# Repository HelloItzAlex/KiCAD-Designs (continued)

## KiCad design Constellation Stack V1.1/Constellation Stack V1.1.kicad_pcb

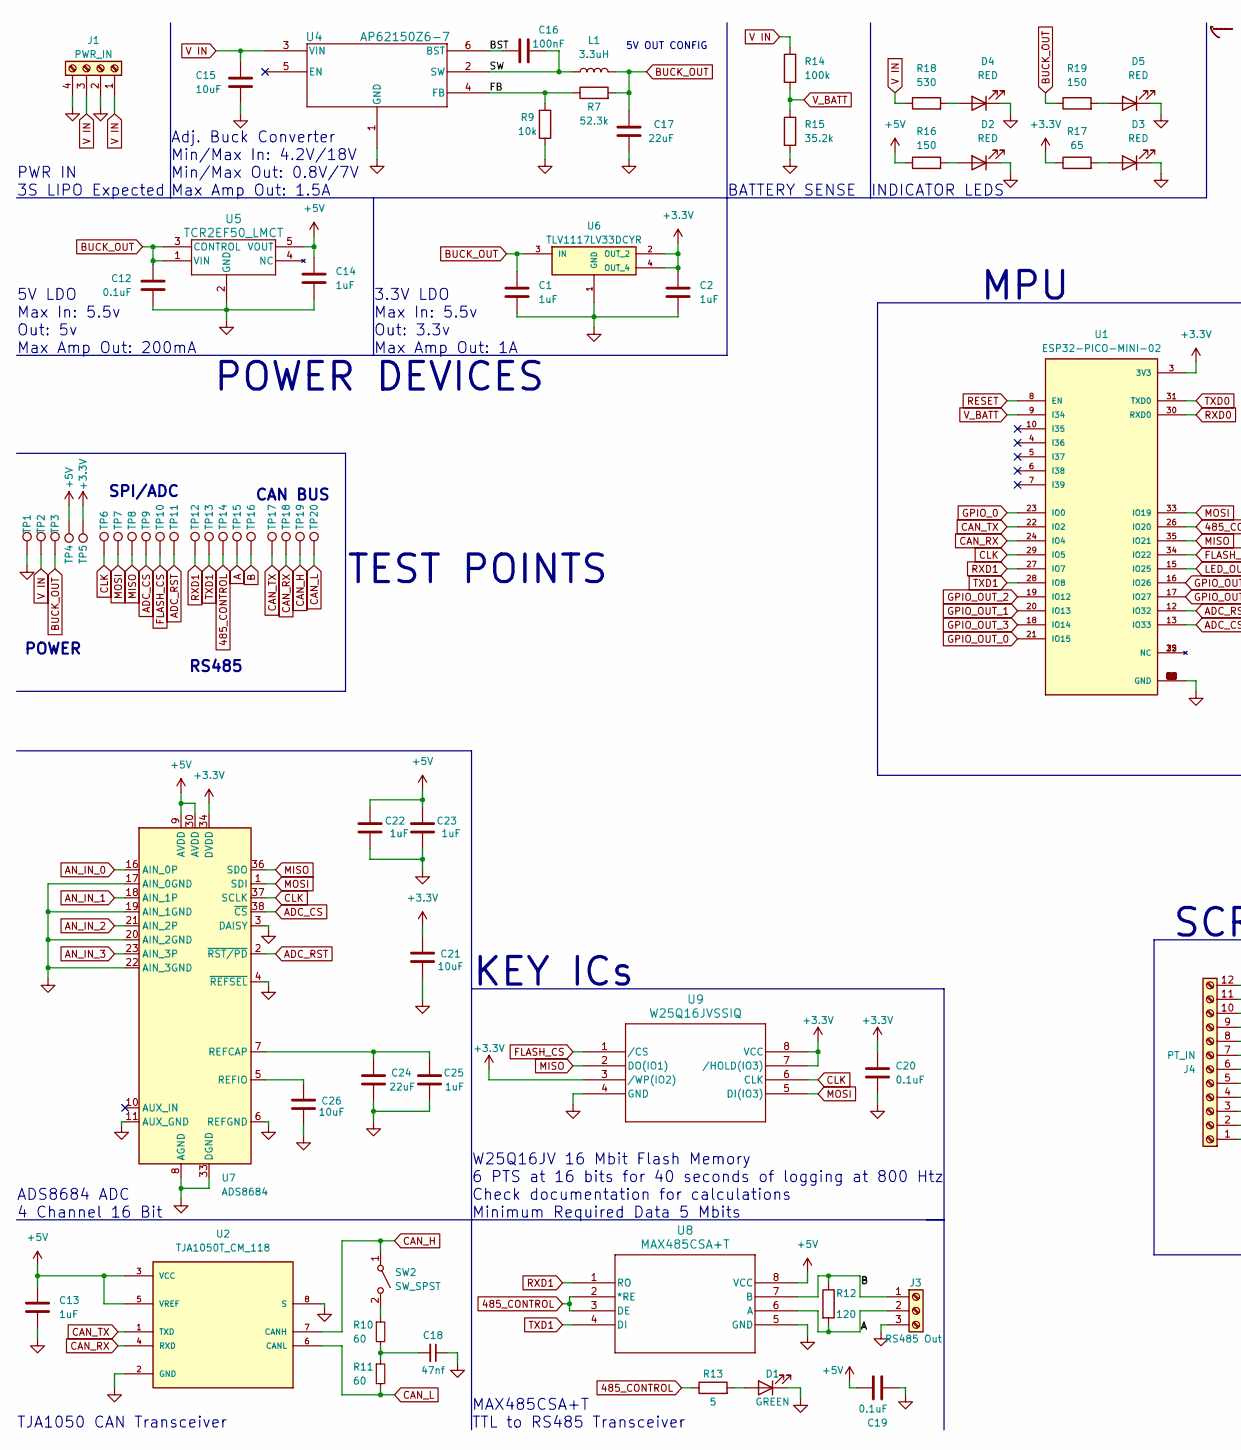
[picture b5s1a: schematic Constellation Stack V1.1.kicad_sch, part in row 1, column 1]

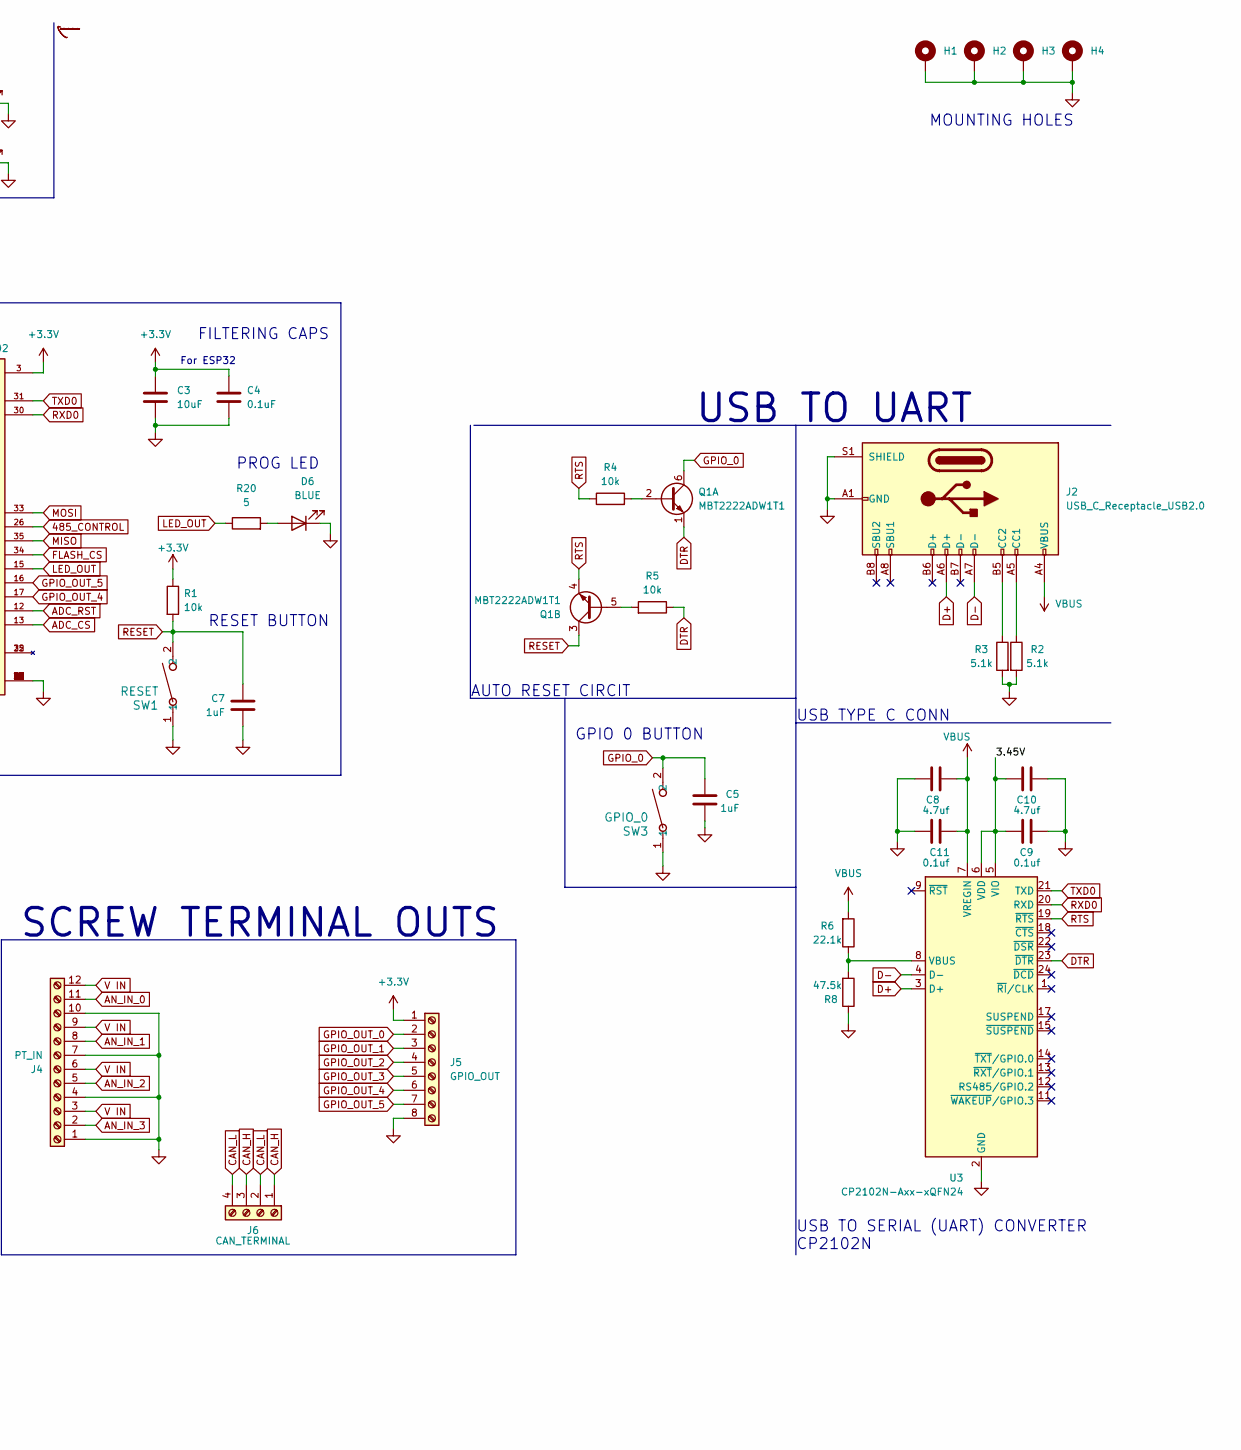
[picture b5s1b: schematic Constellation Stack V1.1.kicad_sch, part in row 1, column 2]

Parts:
C1, C5, C7, C14, C22, C23, C25: 1uF; C_0603_1608Metric
C2: 1uF; C_0805_2012Metric
C3, C21: 10uF; C_0805_2012Metric
C4, C12: 0.1uF; C_0603_1608Metric
C8, C10: 4.7uf; C_0402_1005Metric
C9, C11: 0.1uf; C_0402_1005Metric
C13: 1uF; C_0402_1005Metric
C15: 10uF; C_0402_1005Metric
C16: 100nF; C_0402_1005Metric
C17: 22uF; C_0402_1005Metric
C18: 47nf; C_0402_1005Metric
C19, C20: 0.1uF; C_0402_1005Metric
C24: 22uF; C_1210_3225Metric
C26: 10uF; C_0603_1608Metric
D1: GREEN; LED_0603_1608Metric
D2, D3, D4, D5: RED; LED_0603_1608Metric
D6: BLUE; LED_0603_1608Metric
H1, H2, H3, H4: MountingHole_Pad; MountingHole_3.2mm_M3_DIN965_Pad
J1: PWR_IN; TerminalBlock_Phoenix_MPT-0,5-4-2.54_1x04_P2.54mm_Horizontal
J2: USB_C_Receptacle_USB2.0; USB_C_Receptacle_HCTL_HC-TYPE-C-16P-01A
J3: RS485 Out; TerminalBlock_Phoenix_MPT-0,5-3-2.54_1x03_P2.54mm_Horizontal
J4: PT_IN; TerminalBlock_Phoenix_MPT-0,5-12-2.54_1x12_P2.54mm_Horizont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
J5: GPIO_OUT; TerminalBlock_Phoenix_MPT-0,5-8-2.54_1x08_P2.54mm_Horizontal
J6: CAN_TERMINAL; TerminalBlock_Phoenix_MPT-0,5-4-2.54_1x04_P2.54mm_Horizontal
L1: 3.3uH; L_1008_2520Metric
Q1: MBT2222ADW1T1; SOT-363_SC-70-6
R1, R4, R5, R9: 10k; R_0402_1005Metric
R2, R3: 5.1k; R_0402_1005Metric
R6: 22.1k; R_0402_1005Metric
R7: 52.3k; R_0402_1005Metric
R8: 47.5k; R_0402_1005Metric
R10, R11: 60; R_0805_2012Metric
R12: 120; R_0805_2012Metric
R13, R20: 5; R_0402_1005Metric
R14: 100k; R_0402_1005Metric
R15: 35.2k; R_0402_1005Metric
R16, R19: 150; R_0402_1005Metric
R17: 65; R_0402_1005Metric
R18: 530; R_0402_1005Metric
SW1: RESET; SW_PTS636_CNK
SW2: SW_SPST; SolderJumper-2_P1.3mm_Open_RoundedPad1.0x1.5mm
SW3: GPIO_0; SW_PTS636_CNK
TP1, TP2, TP3, TP4, TP5, TP6, TP7, TP8, TP9, TP10, TP11, TP12, TP13, TP14, TP15, TP16, TP17, TP18, TP19, TP20: TestPoint; TestPoint_Loop_D2.50mm_Drill1.0mm
U1: ESP32-PICO-MINI-02; MODULE_ESP32-PICO-MINI-02; PARTREV v1.0
U2: TJA1050T_CM_118; SOIC127P600X175-8N; PARTREV 4
U3: CP2102N-Axx-xQFN24; QFN-24-1EP_4x4mm_P0.5mm_EP2.7x2.7mm
U4: AP62150Z6-7; TSOT-23-6
U5: TCR2EF50_LMCT; SOT_EF50_LMCT_TOS
U6: TLV1117LV33DCYR; VREG_TLV1117LV33DCYR; PARTREV B
U7: ADS8684; TSSOP-38_4.4x9.7mm_P0.5mm
U8: MAX485CSA+T; 21-0041-3-M_90-0096-8L_MXM
U9: W25Q16JVSSIQ; W25Q16JVSSIQ_WIN

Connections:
485_CONTROL: R13.1, TP14.1, U1.26 (IO20), U8.2 (*RE), U8.3 (DE)
+3.3V: C2.1, C3.1, C4.1, C20.1, C21.2, J5.1, R1.1, R17.1, TP5.1, U1.3 (3V3), U6.2 (OUT_2), U6.4 (OUT_4), U7.34 (DVDD), U9.3 (/WP(IO2)), U9.7 (/HOLD(IO3)), U9.8 (VCC)
+5V: C13.1, C14.1, C19.1, C22.2, C23.2, R16.1, TP4.1, U2.3 (VCC), U2.5 (VREF), U5.5 (VOUT), U7.9 (AVDD), U7.30 (AVDD), U8.8 (VCC)
/3.45V: C9.1, C10.1, U3.5 (VIO), U3.6 (VDD)
/BST: C16.1, U4.6 (BST)
/FB: R7.1, R9.2, U4.4 (FB)
/SW: C16.2, L1.1, U4.2 (SW)
A: J3.2, R12.2, TP15.1, U8.6 (A)
ADC_CS: TP9.1, U1.13 (IO33), U7.38 (~CS)
ADC_RST: TP11.1, U1.12 (IO32), U7.2 (~RST/PD)
AN_IN_0: J4.11, U7.16 (AIN_0P)
AN_IN_1: J4.8, U7.18 (AIN_1P)
AN_IN_2: J4.5, U7.21 (AIN_2P)
AN_IN_3: J4.2, U7.23 (AIN_3P)
B: J3.1, R12.1, TP16.1, U8.7 (B)
BUCK_OUT: C1.1, C12.1, C17.1, L1.2, R7.2, R19.1, TP3.1, U5.1 (VIN), U5.3 (CONTROL), U6.3 (IN)
CAN_H: J6.1, J6.3, SW2.1 (A), TP19.1, U2.7 (CANH)
CAN_L: J6.2, J6.4, R11.2, TP20.1, U2.6 (CANL)
CAN_RX: TP18.1, U1.24 (IO4), U2.4 (RXD)
CAN_TX: TP17.1, U1.22 (IO2), U2.1 (TXD)
CLK: TP6.1, U1.29 (IO5), U7.37 (SCLK), U9.6 (CLK)
D+: J2.A6 (D+), U3.3 (D+)
D-: J2.A7 (D-), U3.4 (D-)
DTR: Q1.1 (E1), R5.1, U3.23 (~DTR)
FLASH_CS: TP10.1, U1.34 (IO22), U9.1 (/CS)
GND: C1.2, C2.2, C3.2, C4.2, C5.2, C7.2, C8.2, C9.2, C10.2, C11.2, C12.2, C13.2, C14.2, C15.2, C17.2, C18.1, C19.2, C20.2, C21.1, C22.1, C23.1, C24.1, C25.1, C26.2, D1.1 (K), D2.1 (K), D3.1 (K), D4.1 (K), D5.1 (K), D6.1 (K), H1.1, H2.1, H3.1, H4.1, J1.2, J1.4, J2.A1 (GND), J2.A12 (GND), J2.B1 (GND), J2.B12 (GND), J2.S1 (SHIELD), J3.3, J4.1, J4.4, J4.7, J4.10, J5.8, R2.2, R3.2, R8.1, R9.1, R15.2, SW1.1, SW3.1, TP1.1, U1.1 (GND), U1.2 (GND), U1.11 (GND), U1.14 (GND), U1.36 (GND), U1.37 (GND), U1.38 (GND), U1.39 (GND), U1.40 (GND), U1.41 (GND), U1.42 (GND), U1.43 (GND), U1.44 (GND), U1.45 (GND), U1.46 (GND), U1.47 (GND), U1.48 (GND), U1.49 (GND), U1.50 (GND), U1.51 (GND), U1.52 (GND), U1.53 (GND), U1.54 (GND), U1.55 (GND), U1.56 (GND), U1.57 (GND), U1.58 (GND), U1.59 (GND), U1.60 (GND), U1.61 (GND), U2.2 (GND), U2.8 (S), U3.2 (GND), U3.25 (GND), U4.1 (GND), U5.2 (GND), U6.1 (GND), U7.3 (DAISY), U7.4 (~REFSEL), U7.6 (REFGND), U7.8 (AGND), U7.11 (AUX_GND), U7.17 (AIN_0GND), U7.19 (AIN_1GND), U7.20 (AIN_2GND), U7.22 (AIN_3GND), U7.28 (AGND), U7.29 (AGND), U7.31 (AGND), U7.32 (AGND), U7.33 (DGND), U8.5 (GND), U9.4 (GND)
GPIO_0: C5.1, Q1.6 (C1), SW3.2, U1.23 (IO0)
GPIO_OUT_0: J5.2, U1.21 (IO15)
GPIO_OUT_1: J5.3, U1.20 (IO13)
GPIO_OUT_2: J5.4, U1.19 (IO12)
GPIO_OUT_3: J5.5, U1.18 (IO14)
GPIO_OUT_4: J5.6, U1.17 (IO27)
GPIO_OUT_5: J5.7, U1.16 (IO26)
LED_OUT: R20.1, U1.15 (IO25)
MISO: TP8.1, U1.35 (IO21), U7.36 (SDO), U9.2 (DO(IO1))
MOSI: TP7.1, U1.33 (IO19), U7.1 (SDI), U9.5 (DI(IO3))
unnamed: C18.2, R10.2, R11.1
unnamed: D1.2 (A), R13.2
unnamed: D2.2 (A), R16.2
unnamed: D3.2 (A), R17.2
unnamed: D4.2 (A), R18.2
unnamed: D5.2 (A), R19.2
unnamed: D6.2 (A), R20.2
unnamed: J2.A5 (CC1), R2.1
unnamed: J2.B5 (CC2), R3.1
unnamed: Q1.2 (B1), R4.2
unnamed: Q1.5 (B2), R5.2
unnamed: R10.1, SW2.2 (B)
unnamed: R6.1, R8.2, U3.8 (VBUS)
unnamed: C24.2, C25.2, U7.7 (REFCAP)
unnamed: C26.1, U7.5 (REFIO)
RESET: C7.1, Q1.3 (C2), R1.2, SW1.2, U1.8 (EN)
RTS: Q1.4 (E2), R4.1, U3.19 (~RTS)
RXD0: U1.30 (RXD0), U3.20 (RXD)
RXD1: TP12.1, U1.27 (IO7), U8.1 (RO)
TXD0: U1.31 (TXD0), U3.21 (TXD)
TXD1: TP13.1, U1.28 (IO8), U8.4 (DI)
V IN: C15.1, J1.1, J1.3, J4.3, J4.6, J4.9, J4.12, R14.1, R18.1, TP2.1, U4.3 (VIN)
VBUS: C8.1, C11.1, J2.A4 (VBUS), J2.A9 (VBUS), J2.B4 (VBUS), J2.B9 (VBUS), R6.2, U3.7 (VREGIN)
V_BATT: R14.2, R15.1, U1.9 (I34)

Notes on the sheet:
BATTERY SENSE
MPU
For ESP32
USB TO UART
TEST POINTS
USB TO SERIAL (UART) CONVERTER CP2102N
RESET BUTTON
POWER
ADS8684 ADC 4 Channel 16 Bit
Adj. Buck Converter Min/Max In: 4.2V/18V Min/Max Out: 0.8V/7V Max Amp Out: 1.5A
SCREW TERMINAL OUTS
W25Q16JV 16 Mbit Flash Memory 6 PTS at 16 bits for 40 seconds of logging at 800 Htz Check documentation for calculations Minimum Required Data 5 Mbits
SPI/ADC
FILTERING CAPS
MAX485CSA+T TTL to RS485 Transceiver
3.3V LDO Max In: 5.5v Out: 3.3v Max Amp Out: 1A
TJA1050 CAN Transceiver
RS485
PROG LED
INDICATOR LEDS
CAN BUS
POWER DEVICES
AUTO RESET CIRCIT
PWR IN 3S LIPO Expected
5V LDO Max In: 5.5v Out: 5v Max Amp Out: 200mA
USB TYPE C CONN
GPIO 0 BUTTON
MOUNTING HOLES
5V OUT CONFIG
KEY ICs

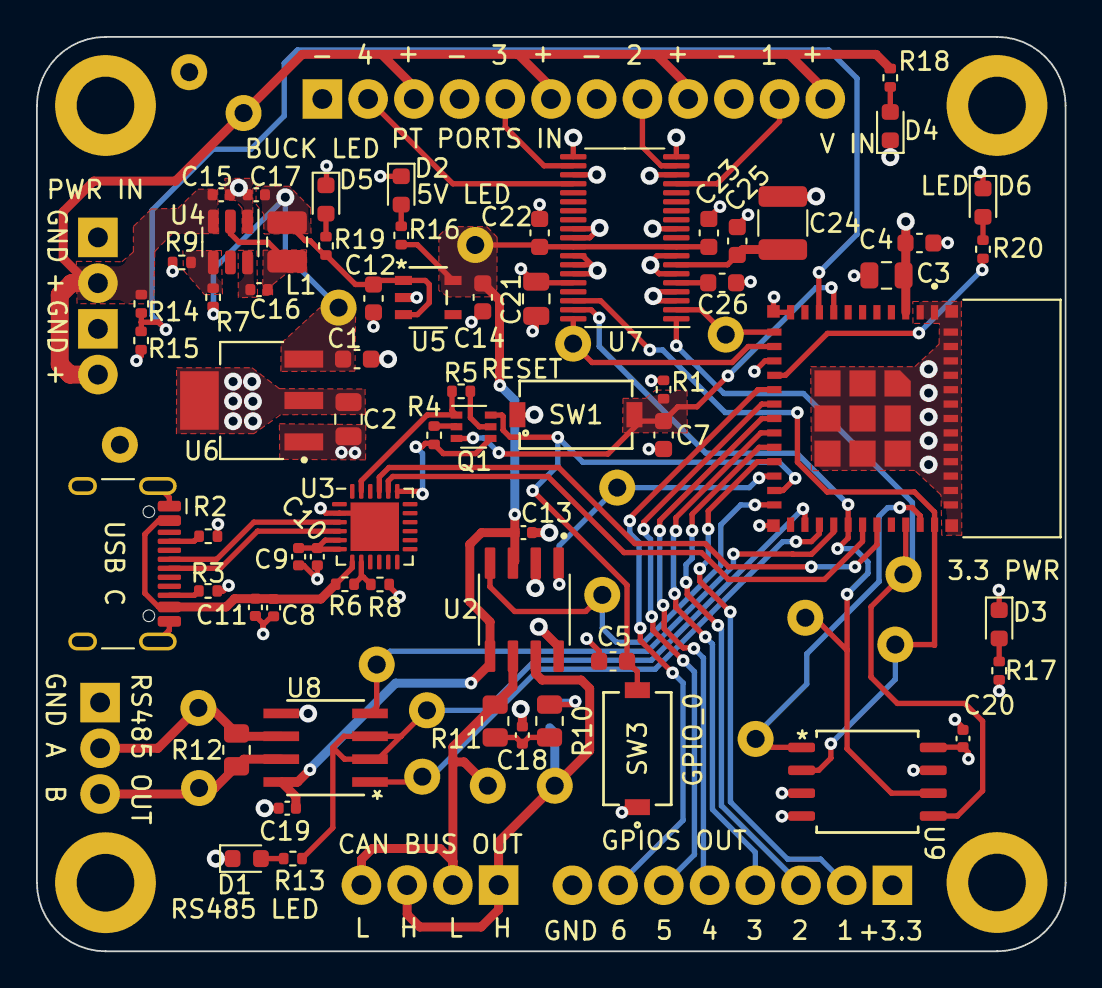
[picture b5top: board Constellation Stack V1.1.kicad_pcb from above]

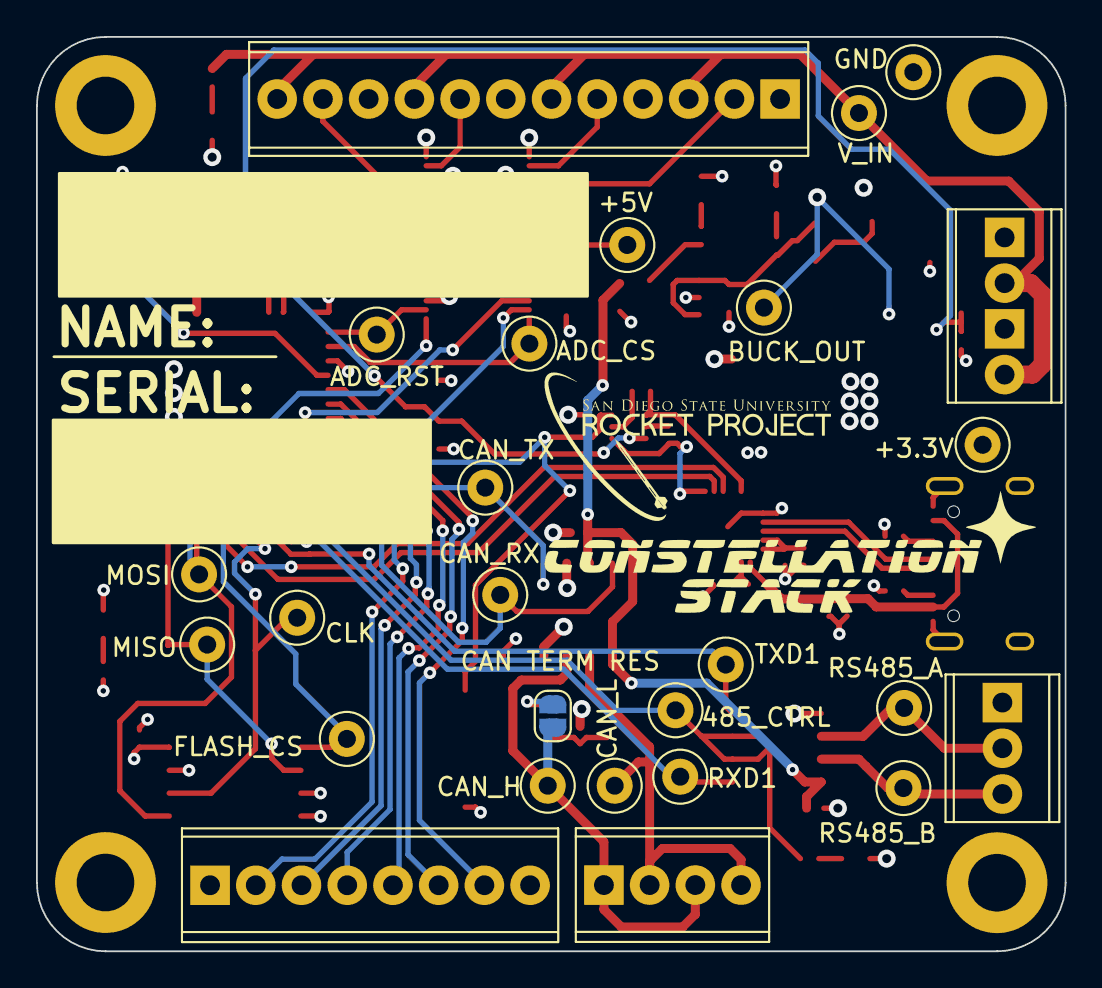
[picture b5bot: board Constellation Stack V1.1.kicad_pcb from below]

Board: 4 copper layers, 57.1 x 50.8 mm, 95 parts (26 on the bottom side), 60 nets.
